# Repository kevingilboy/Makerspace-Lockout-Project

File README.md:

# Makerspace Lockout Project
Makerspace staff exert much of their time watching over students and verifying safety training… a process that is mundane, imperfect, and begs for automation.
Our motivation was to non-obtrusively enforce the safe and sustainable use of machinery in the Makerspaces across campus through RF student ID verification against a user database - if a student is not trained, power is cut to the tool and it will not turn on. If a student is trained, the tool is enabled.

[Video](https://www.youtube.com/watch?v=2HG-vyV4yoM)

[Poster](https://github.com/kevingilboy/Makerspace-Lockout-Project/blob/main/Design%20Expo%20Poster.pdf)

## System Usage Diagram
The system is diagrammed below. A Raspberry Pi acts as a Wi-Fi access point and MQTT broker for Arduino microcontrollers in the Makerspace, and it communicates with the external database to authenticate users trying to enable tools. The complete workflow is as follows (please watch the [Video](https://www.youtube.com/watch?v=2HG-vyV4yoM) above for the simpler workflow. It is much easier to "show" this project than to "tell" about it).
1. A user inserts their ID into the 3D printed "Card Holder". The Holder holds the card such that the RFID element hovers over an RFID reader. A Wi-Fi Arduino inside the Holder detects that a card has been placed and reads the UUID from the student ID.
2. The Wi-Fi Arduino publishes a MQTT message to the Raspberry Pi in the room asking for user authentication, and notifies it which tool the user is trying to use. The Arduino changes a status LED to yellow to signify that authentication is underway.
3. The Pi asks the main Makerspace server if the user is authenticated for the given tool and the server responds.
4. An optional buddy system is also supported in that a tool can require a room administrator to put their card in a separate "buddy" Card Holder.
5. If authenticated (and a buddy is present if required), the Pi publishes a MQTT message to a separate Wi-Fi Arduino that controls power to the tool via a 120V relay. The Card Holder Arduino also receives this message and changes the status LED to green to signify that the user is authenticated.
6. The Arduino enables the tool through the relay and the user can do their work. The system can detect if the tool is prematurely switched on as it turns on the relay (e.g. if the previous person forgot to turn off the tool and simply grabbed their ID and left), and quickly switches the relay off as a failsafe. A buzzer makes noise to let the user know to switch off the tool for the relay to be enabled.
7. If a user leaves their ID on a Card Reader but does not power on the machine for a certain time threshold, an email is sent to them stating that they either forgot their ID on the Card Reader or are being unsafe by leaving tools enabled and unused for long periods of time.
8. When the user is finished, they take their ID off the Card Reader, which turns the status light to red and triggers a MQTT message from the Card Reader to the Pi, which then publishes a MQTT message to the relay-controlling Arduino to turn off the relay. If the user takes their ID off the reader without switching off the tool (as detected through current monitoring), a buzzer makes noise and power to the relay is cut.

## Materials for One Connected Tool
| Component      | Quantity | Total Cost
| ----------- | ----------- | ---------
| Wi-Fi Arduino MCU (ESP8266)      | 2       | $20
| RFID Reader (MFRC522)   | 1        | $5
| RGB LED (Adafruit Neopixel)   | 1        | $1
| Relay (PowerSwitch Tail II)   | 1        | $26
| Current Sensor (30A Split Core from Sparkfun)   | 1        | $10
| Piezo Alarm (Optional)   | 1        | $3
| Power supply for MCUs | 2 | $10
| Assorted jumpers | |
| PCB board | |
| 3D printer filament | |
| Some sort of metal lock box? | |
| | | $75

## Materials for One Connected Makerspace
| Component      | Quantity | Total Cost
| ----------- | ----------- | -----
| Raspberry Pi 3      | 1       | $35
| 2A Wall Adapter Power Supply (USB Micro-B) |1 | $8
| | | $43

## State of the Repo
All arduino code has been uploaded

All EAGLE PCB CAD files have been uploaded

All SolidWorks CAD files have been uploaded

In-Room Pi Access Point files have been uploaded - SD card image available by request

The Database has been defined but the external server code has not been uploaded

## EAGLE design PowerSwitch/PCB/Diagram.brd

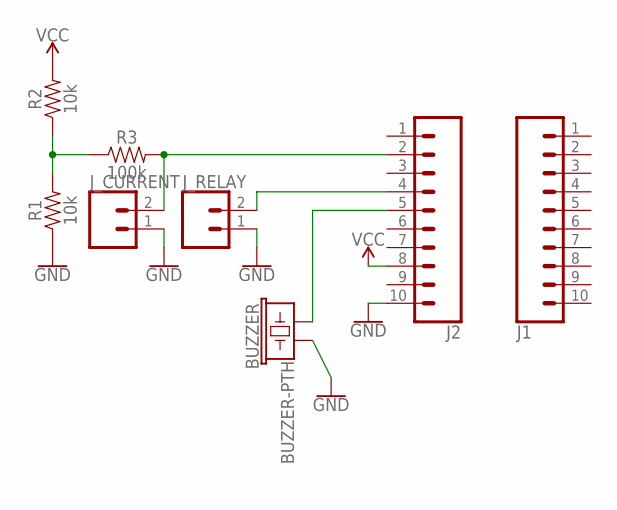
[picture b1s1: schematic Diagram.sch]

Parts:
BUZZER: BUZZER-PTH; BUZZER-12MM
J1, J2: CONN_10"; 1X10
J_CURRENT: CONN_02; 1X02
J_RELAY: CONN_02; 1X02
R1, R2: 10k; AXIAL-0.3
R3: 100k; AXIAL-0.3

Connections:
A: J2.2, J_CURRENT.2, R3.P$2 (2)
GND: BUZZER.- (2), J2.10, J_CURRENT.1, J_RELAY.1, R1.P$1 (1)
unnamed: R1.P$2 (2), R2.P$1 (1), R3.P$1 (1)
unnamed: J2.4, J_RELAY.2
PIN14: BUZZER.+ (1), J2.5
VCC: J2.8, R2.P$2 (2)

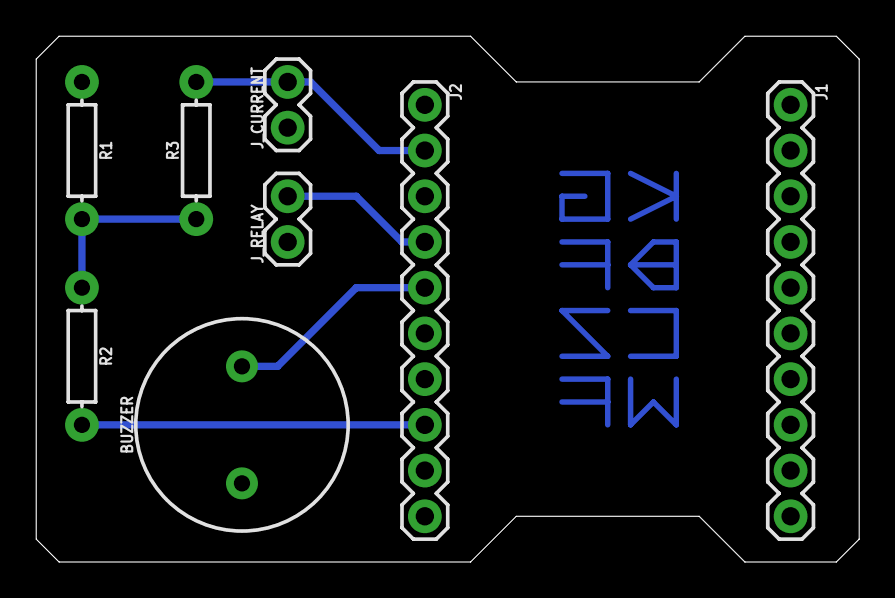
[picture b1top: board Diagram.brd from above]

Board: 2 copper layers, 45.7 x 29.2 mm, 8 parts (0 on the bottom side), 6 nets.

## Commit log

2021-02-02 Created repository and added Expo Poster
2021-02-02 Added ID holster CAD
2021-02-02 Updated rendering path in readme
2021-02-02 Added ID holster arduino code
2021-02-02 Renamed folder to Card Reader
2021-02-02 Added admin card reader
2021-02-02 Added PCB files
2021-02-02 Added PowerSwitch arduino
2021-02-02 Changed name of PowerSwitch directory
2021-02-02 Fixing directory naming
2021-02-02 Re-added PowerSwitch directory
2021-02-25 Added all card reader CAD files
2021-02-25 Updated main README.md
2021-02-25 Updated README photo
2021-02-25 Added linux network config files
2021-02-25 Added NodeJS site

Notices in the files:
parts and their libraries:
SparkFun-Electromechanical: Licensing: Creative Commons ShareAlike 4.0 International - https://creativecommons.org/licenses/by-sa/4.0
